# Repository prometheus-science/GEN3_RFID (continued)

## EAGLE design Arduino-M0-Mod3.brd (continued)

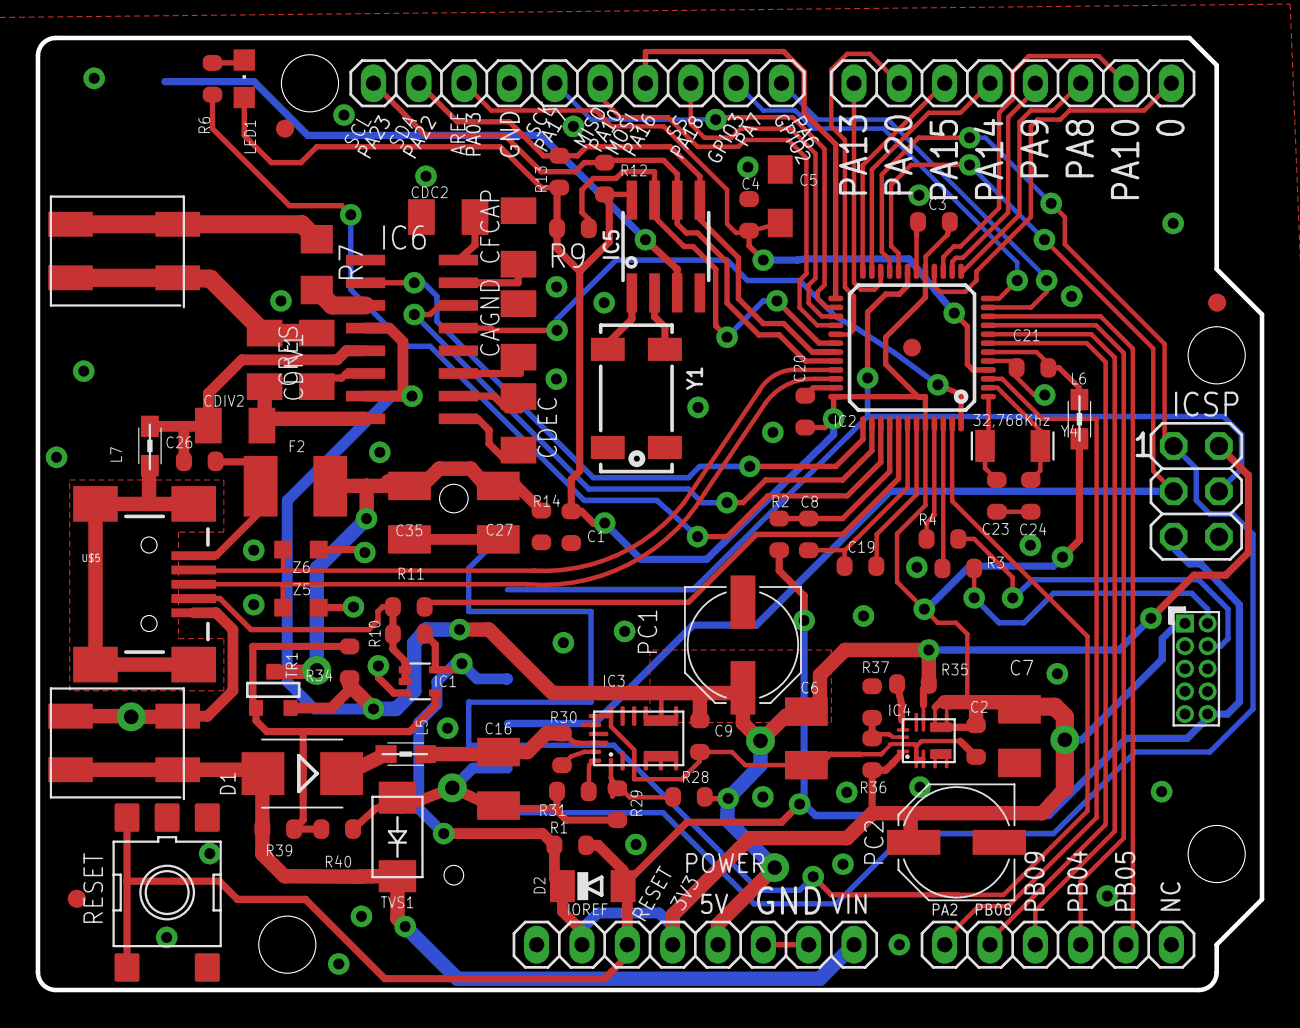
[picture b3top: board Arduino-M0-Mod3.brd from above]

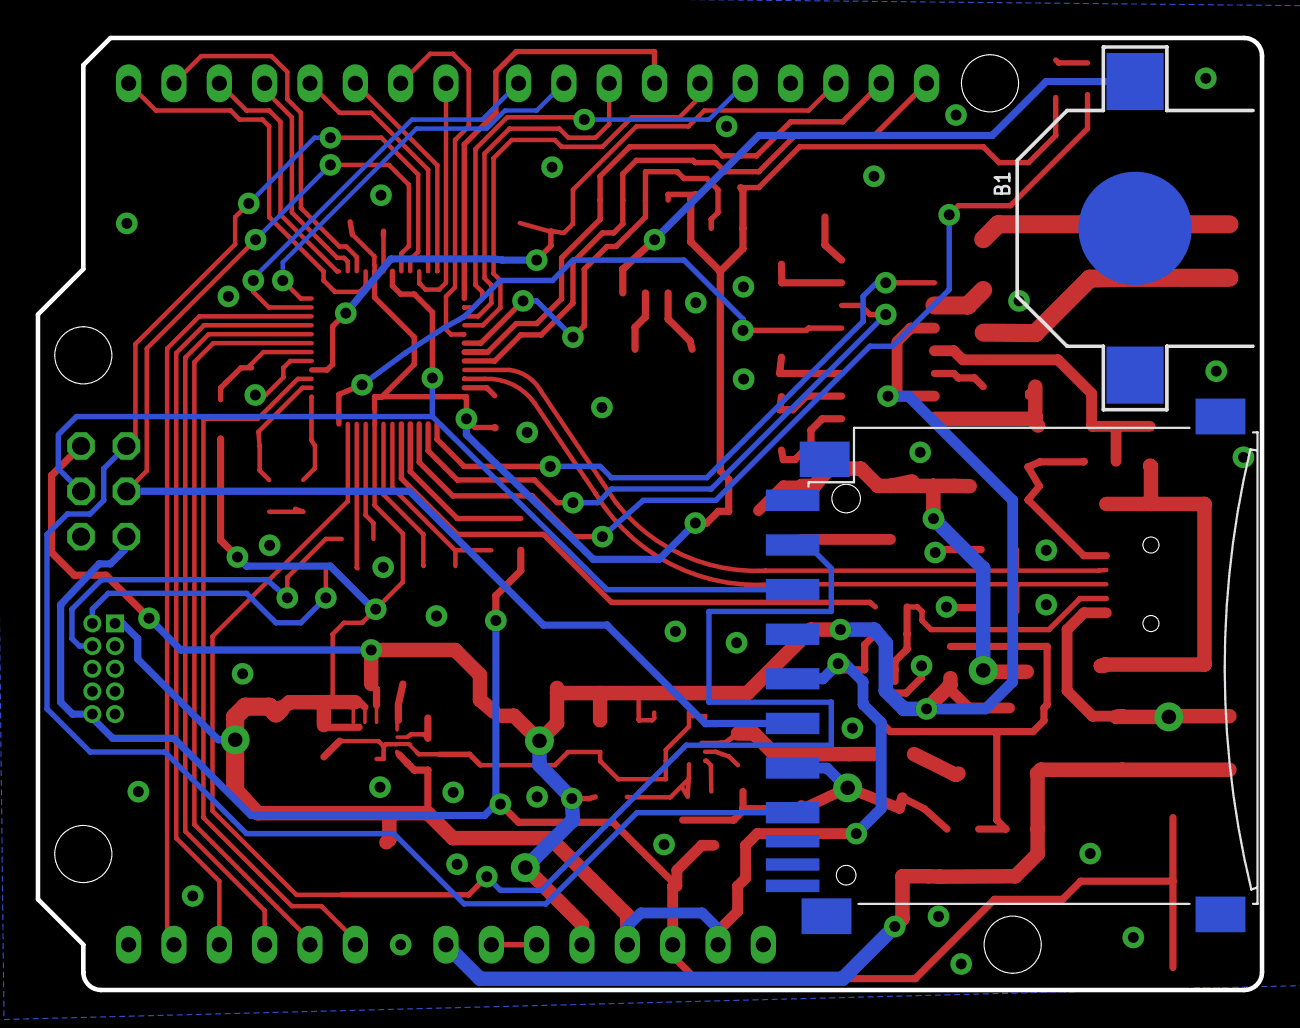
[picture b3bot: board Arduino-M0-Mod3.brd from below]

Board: 4 copper layers, 68.6 x 53.3 mm, 110 parts (2 on the bottom side), 74 nets.

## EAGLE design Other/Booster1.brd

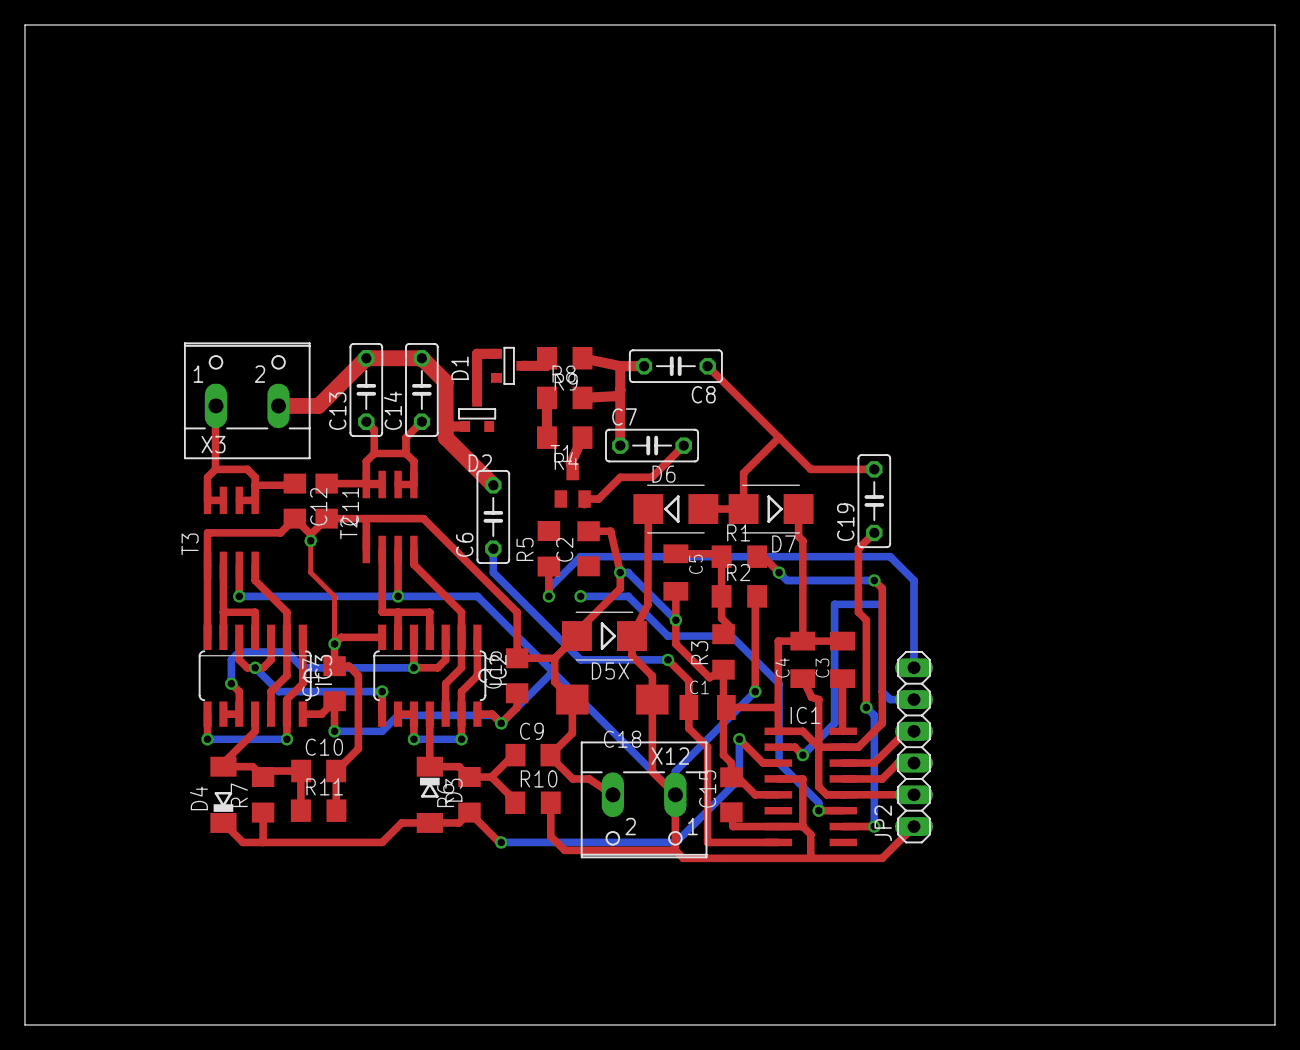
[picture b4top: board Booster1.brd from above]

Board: 2 copper layers, 100.0 x 80.0 mm, 46 parts (0 on the bottom side), 33 nets.

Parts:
C1: C1206K
C2: 150nF; C1206
C3: 22nF; C1206K
C4, C5: 10nF; C1206K
C6: 47pF; C050-025X075
C7: 1nF; C050-025X075
C8: 100nF; C050-025X075
C9, C10, C11, C12: 47pF; C1206
C13, C14: C050-025X075
C15, C16, C17: 100nF; C1206
C18: 100uF; CT7343
C19: 1uF; C050-025X075
D1, D2: BAS21; SOT-23
D3, D4: LL4148; SOD106-R
D5X: SM6T6V8A; SMB
D6, D7: SMB
IC1: EM4095; SO16
IC2, IC3: 74HC14D; SO14
JP2: 1X06
R1, R4, R8: 1M; R1206
R2: 6K; R1206
R3: 4K; R1206
R5: 10K; R1206
R6, R7: 2.2K; R1206
R9, R10, R11: 4.7K; R1206
T1: BC846; SOT23
T2, T3: IRF8313P; SO-08
X3, X12: W237-102

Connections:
+5V: C15.1, C16.1, C17.1, C18.+, D5X.C, D6.C, IC1.4, IC1.7, IC2.14, IC3.14, JP2.1, R2.2, R10.2, T2.3, T3.3, X12.1
ANT1: D3.A, D4.C, IC1.3, R6.1, R7.1
BANT2: C12.1, T3.5, T3.6, T3.7, T3.8, X3.1
DMOD: IC1.13, JP2.3
GND: C1.2, C2.2, C3.2, C4.2, C5.2, C7.2, C9.2, C10.2, C11.2, C12.2, C15.2, C16.2, C17.2, C18.-, D5X.A, D7.C, IC1.1, IC1.5, IC1.12, IC2.7, IC3.7, JP2.2, R3.1, R11.2, T1.2, T2.1, T3.1, X12.2
unnamed: C10.1, D4.A, IC3.11, R7.2, R11.1
unnamed: IC2.1, IC2.9, IC2.10, IC2.13
unnamed: D1.3, D2.1
unnamed: IC2.8, IC3.3, IC3.5
unnamed: IC2.3, IC2.5, IC3.9, IC3.10
unnamed: IC2.4, IC2.6, T2.2
unnamed: IC2.2, IC2.12, T2.4
unnamed: IC3.1, IC3.8, IC3.13
unnamed: IC3.2, IC3.12, T3.4
unnamed: IC3.4, IC3.6, T3.2
unnamed: C9.1, D3.C, IC2.11, R6.2, R10.1
unnamed: C11.1, C13.1, C14.1, T2.5, T2.6, T2.7, T2.8
unnamed: D1.1, R9.2
unnamed: C4.1, IC1.15, R1.2
unnamed: C2.1, IC1.11
unnamed: C5.1, R1.1, R2.1, R3.2
unnamed: C3.1, IC1.16
unnamed: C19.1, IC1.10
unnamed: C7.1, C8.2, R8.2, R9.1
unnamed: R4.2, R8.1
unnamed: C8.1, C19.2, D6.A, D7.A
unnamed: R4.1, T1.3
unnamed: R5.2, T1.1
unnamed: JP2.6, R5.1
RDY: IC1.2, JP2.5
SLP: IC1.14, JP2.4
X3.TAB: C6.2, C13.2, C14.2, D2.3, X3.2
XXX: C1.1, C6.1, IC1.8

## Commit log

2017-02-10 Mod3 traces complete
2017-02-17 Mod4 conceptual prototype
2017-02-20 Conceptual prototype 2 minor board edits
2017-03-06 Mod5 conceptual prototype with dual antenna and power supply
2017-03-08 Moved files around Added pin layout sheet
2017-03-08 Updated pin mapping list
2017-03-13 MArch13_PFETs added and pins rearranged
2017-03-15 Added 3.3V regulator for USB operation
2017-03-20 Jay's changes to voltage regulator
2017-04-05 dual level mosfet added to voltage divider
2017-04-11 Design submitted to PCB shop
2017-05-10 Design submitted to PCB shop update
2019-05-12 Removed old design files
2019-05-12 Updated files...
2021-04-26 cponvert board to kicad and prepare for kitspace
